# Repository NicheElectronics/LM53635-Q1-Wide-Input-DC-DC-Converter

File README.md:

# LM53635-Q1 Wide-Input DC-DC Converter

A four-layer, **5 V / 3.5 A design-target** synchronous buck converter built around the Texas Instruments **LM53635-Q1**. The board is intended for a **6–36 V input** and provides a choice of direct or EMI-filtered input paths for evaluating power-supply behavior.

> **Status:** PCB design and PSpice simulation are complete. The board has not yet been fabricated or electrically validated. The voltage, current, efficiency and EMI performance described here are design goals, not measured results.

## At a glance

| Item | Design |
| --- | --- |
| Controller | TI LM53635-Q1 automotive synchronous step-down converter |
| Intended input | 6–36 V DC |
| Intended output | 5 V, up to 3.5 A design target |
| PCB | Four layers, designed in KiCad |
| Input options | Direct path and EMI-filtered path |
| Analysis | PSpice startup and steady-state/transient simulations |
| Hardware verification | Pending fabrication and bench measurements |

The **6–36 V** range is this board's intended range. The IC's own operating limits and transient ratings are specified in the [TI LM53635-Q1 datasheet](https://www.ti.com/product/LM53635-Q1); they should not be treated as a measured rating of the assembled board.

## Design overview

```mermaid
flowchart LR
    VIN["6–36 V input"] --> PATH["Direct or filtered input"]
    PATH --> BUCK["LM53635-Q1 buck stage"]
    BUCK --> OUT["5 V output"]
```

The layout emphasizes a compact switching-current loop, local decoupling, sensible AGND/GND handling, input filtering and accessible measurement points. The filtered and direct input options support comparison during later EMI and transient testing. The project files include KiCad hardware data, manufacturing outputs, board renders and PSpice work; consult those source files for exact component values and connector pinouts.

## Simulation and validation

Startup and transient behavior have been examined in **PSpice for TI**. Simulation helps check the design before fabrication but does not establish hardware output ripple, efficiency, thermal behavior or emissions.

Once a board is assembled, the planned checks are:

1. Inspect assembly, polarity and resistance between each power rail and ground.
2. Power the board from a current-limited bench supply and verify the 5 V output at light load.
3. Check startup and output regulation across the intended input range and representative loads.
4. Measure ripple, load-transient response and component temperature; record the instruments and test conditions.
5. Compare direct and filtered input paths and evaluate conducted EMI with a suitable measurement setup.

No bench measurements or compliance results are claimed at this stage.

## Design files and reference

The repository contains the schematic, PCB design, manufacturing material, renders and simulation results. Use the **KiCad source files** as the authority for the actual revision and the [TI datasheet](https://www.ti.com/product/LM53635-Q1) for device limits and recommended layout practice.

## Author

**Nishant Patil**

No license has been specified for the project files. Add one if you want to define reuse terms.

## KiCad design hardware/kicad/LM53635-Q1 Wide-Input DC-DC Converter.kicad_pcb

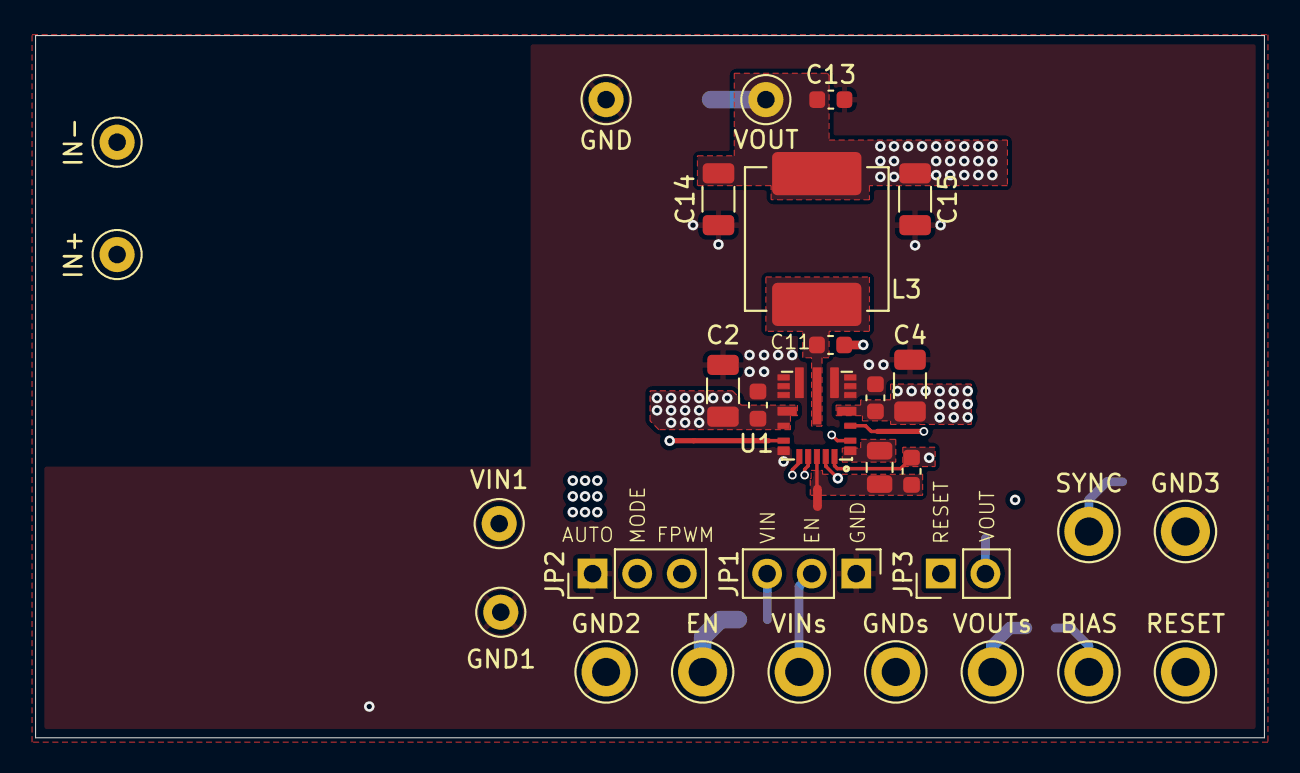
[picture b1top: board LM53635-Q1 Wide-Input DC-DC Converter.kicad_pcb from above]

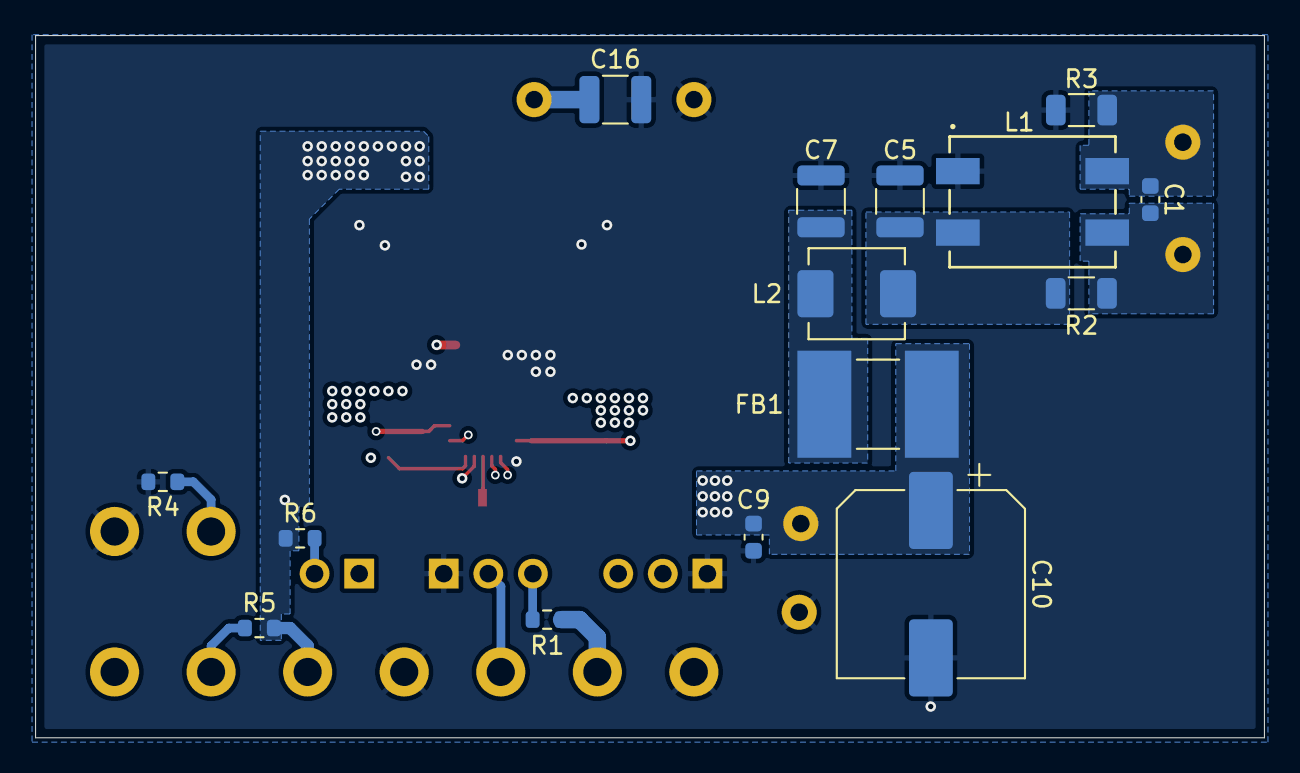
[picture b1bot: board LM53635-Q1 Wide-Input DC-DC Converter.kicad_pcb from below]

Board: 4 copper layers, 70.0 x 40.0 mm, 46 parts (15 on the bottom side), 18 nets.

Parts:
BIAS: TestPoint; TestPoint_Keystone_5005-5009_Compact
C1, C9, C12, C13: 0.1uF; C_0603_1608Metric
C2, C4: 10uF; C_1206_3216Metric
C3, C6: 0.047uF; C_0603_1608Metric
C5, C7: 4.7uF; C_1210_3225Metric
C8: 4.7uF; C_0805_2012Metric
C10: 100uF; CP_Elec_10x10.5
C11: 0.47uF; C_0603_1608Metric
C14, C15: 22uF; C_1206_3216Metric
C16: 47uF; C_1210_3225Metric
EN: TestPoint; TestPoint_Keystone_5005-5009_Compact
FB1: 600 ohm; FB_HI2220P601R-10
GND, GND1: TestPoint; TestPoint_Keystone_5000-5004_Miniature
GND2, GND3: TestPoint; TestPoint_Keystone_5005-5009_Compact
GNDs: TestPoint; TestPoint_Keystone_5005-5009_Compact
IN+: TestPoint; TestPoint_Keystone_5000-5004_Miniature
IN-: TestPoint; TestPoint_Keystone_5000-5004_Miniature
JP1: EN Jumper; PinHeader_1x03_P2.54mm_Vertical
JP2: FPWM Jumper; PinHeader_1x03_P2.54mm_Vertical
JP3: Reset Jumper; PinHeader_1x02_P2.54mm_Vertical
L1: ACM9070-701-2PL-TL01; IND_ACM9070_TDK
L2: 2.2uH; INDM5451X300N
L3: 2.2uH; INDM8681X400N
NT1: NetTie_2; NetTie-2_SMD_Pad0.5mm
R1, R4, R6: 100K; R_0603_1608Metric
R2, R3: 0R; R_1206_3216Metric
R5: 3R; R_0603_1608Metric
RESET: TestPoint; TestPoint_Keystone_5005-5009_Compact
SYNC: TestPoint; TestPoint_Keystone_5005-5009_Compact
U1: LM536353QRNLRQ1; CONV_LMS3655MMRNLR
VIN1: TestPoint; TestPoint_Keystone_5000-5004_Miniature
VINs: TestPoint; TestPoint_Keystone_5005-5009_Compact
VOUT: TestPoint; TestPoint_Keystone_5000-5004_Miniature
VOUTs: TestPoint; TestPoint_Keystone_5005-5009_Compact

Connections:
/BIAS: BIAS.1, C12.1, R5.1, U1.22 (BIAS)
/BOOT: C11.1, U1.2 (CBOOT)
/EN: JP1.2 (C), U1.18 (EN), VINs.1
/FPWM: JP2.2 (C), U1.16 (FPWM)
/RESET: JP3.1 (A), RESET.1, U1.19 (RESET_N)
/SW: C11.2, L3.1, U1.9 (SW)
/SYNC: R4.1, SYNC.1, U1.3 (SYNC)
GND: C2.2, C3.2, C4.2, C5.2, C6.2, C7.2, C9.2, C10.2, C13.2, C14.2, C15.2, C16.2, GND.1, GND1.1, GND2.1, GND3.1, GNDs.1, JP1.1 (A), JP2.1 (A), L1.1, NT1.2, R3.2, R4.2, U1.5 (PGND1), U1.6 (PGND1), U1.7 (PGND1), U1.8 (PGND1), U1.10 (PGND2), U1.11 (PGND2), U1.12 (PGND2), U1.13 (PGND2), U1.17 (NC)
GNDA: C8.1, C12.2, NT1.1, U1.20 (AGND)
unnamed: C1.1, IN+.1, L1.3, R2.1
unnamed: C1.2, IN-.1, L1.4, R3.1
unnamed: C5.1, L1.2, L2.1, R2.2
unnamed: C7.1, FB1.1, L2.2
unnamed: JP1.3 (B), R1.1
unnamed: JP3.2 (B), R6.2
unnamed: C8.2, U1.1 (VCC)
VIN: C2.1, C3.1, C4.1, C6.1, C9.1, C10.1, EN.1, FB1.2, JP2.3 (B), R1.2, U1.4 (PVIN1), U1.14 (PVIN2), U1.15 (AVIN), VIN1.1
VOUT: C13.1, C14.1, C15.1, C16.1, L3.2, R5.2, R6.1, U1.21 (FB), VOUT.1, VOUTs.1

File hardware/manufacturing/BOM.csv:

"Reference","Qty","Value","DNP","Exclude from BOM","Exclude from Board","Footprint","Datasheet"
"BIAS1,EN1,GND2,GND3,GNDs1,RESET1,SYNC1,VINs1,VOUTs1","9","TestPoint","","","","TestPoint:TestPoint_Keystone_5005-5009_Compact","~"
"C1,C9,C12,C13","4","0.1uF","","","","Capacitor_SMD:C_0603_1608Metric","~"
"C2,C4","2","10uF","","","","Capacitor_SMD:C_1206_3216Metric","~"
"C3,C6","2","0.047uF","","","","Capacitor_SMD:C_0603_1608Metric","~"
"C5,C7","2","4.7uF","","","","Capacitor_SMD:C_1210_3225Metric","~"
"C8","1","4.7uF","","","","Capacitor_SMD:C_0805_2012Metric","~"
"C10","1","100uF","","","","Capacitor_SMD:CP_Elec_10x10.5",""
"C11","1","0.47uF","","","","Capacitor_SMD:C_0603_1608Metric","~"
"C14,C15","2","22uF","","","","Capacitor_SMD:C_1206_3216Metric","~"
"C16","1","47uF","","","","Capacitor_SMD:C_1210_3225Metric","~"
"FB1","1","600 ohm","","","","HI2220P601R-10:FB_HI2220P601R-10","~"
"GND1,GND4,IN+1,IN-1,VIN1,VOUT1","6","TestPoint","","","","TestPoint:TestPoint_Keystone_5000-5004_Miniature","~"
"JP1","1","EN Jumper","","Excluded from BOM","","Connector_PinHeader_2.54mm:PinHeader_1x03_P2.54mm_Vertical","~"
"JP2","1","FPWM Jumper","","Excluded from BOM","","Connector_PinHeader_2.54mm:PinHeader_1x03_P2.54mm_Vertical","~"
"JP3","1","Reset Jumper","","","","Connector_PinHeader_2.54mm:PinHeader_1x02_P2.54mm_Vertical","~"
"L1","1","ACM9070-701-2PL-TL01","","","","ACM9070-701-2PL-TL01:IND_ACM9070_TDK","ACM9070-701-2PL-TL01"
"L2","1","2.2uH","","","","IHLP2020CZER2R2M11:INDM5451X300N","~"
"L3","1","2.2uH","","","","IHLP3232DZER2R2M11:INDM8681X400N","~"
"NT1","1","NetTie_2","","Excluded from BOM","","NetTie:NetTie-2_SMD_Pad0.5mm","~"
"R1,R4,R6","3","100K","","","","Resistor_SMD:R_0603_1608Metric","~"
"R2,R3","2","0R","","","","Resistor_SMD:R_1206_3216Metric","~"
"R5","1","3R","","","","Resistor_SMD:R_0603_1608Metric","~"
"U1","1","LM536353QRNLRQ1","","","","LM53635LQRNLTQ1:CONV_LMS3655MMRNLR","https://www.ti.com/lit/gpn/lm53635-q1"
